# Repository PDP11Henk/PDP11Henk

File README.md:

- 👋 Hi, I’m @PDP11Henk, also a HAM radio amateur with the call-sign PA8PDP.
- 👀 I’m interested in building an F-16 simulator, building and playing with the Motorola 68000 / 68010 / 68020 microprocessors, and collecting PDP-11 hardware from D|I|G|I|T|A|L
- 🌱 I’m currently learning how to use Git  :) 
- 💞️ I’m looking to collaborate on integrating F-16 real instruments with home-made interface hardware to the Benchmark Systems BMS Simulator.
- 📫 How to reach me ...

<!---
PDP11Henk/PDP11Henk is a ✨ special ✨ repository because its `README.md` (this file) appears on your GitHub profile.
You can click the Preview link to take a look at your changes.
--->

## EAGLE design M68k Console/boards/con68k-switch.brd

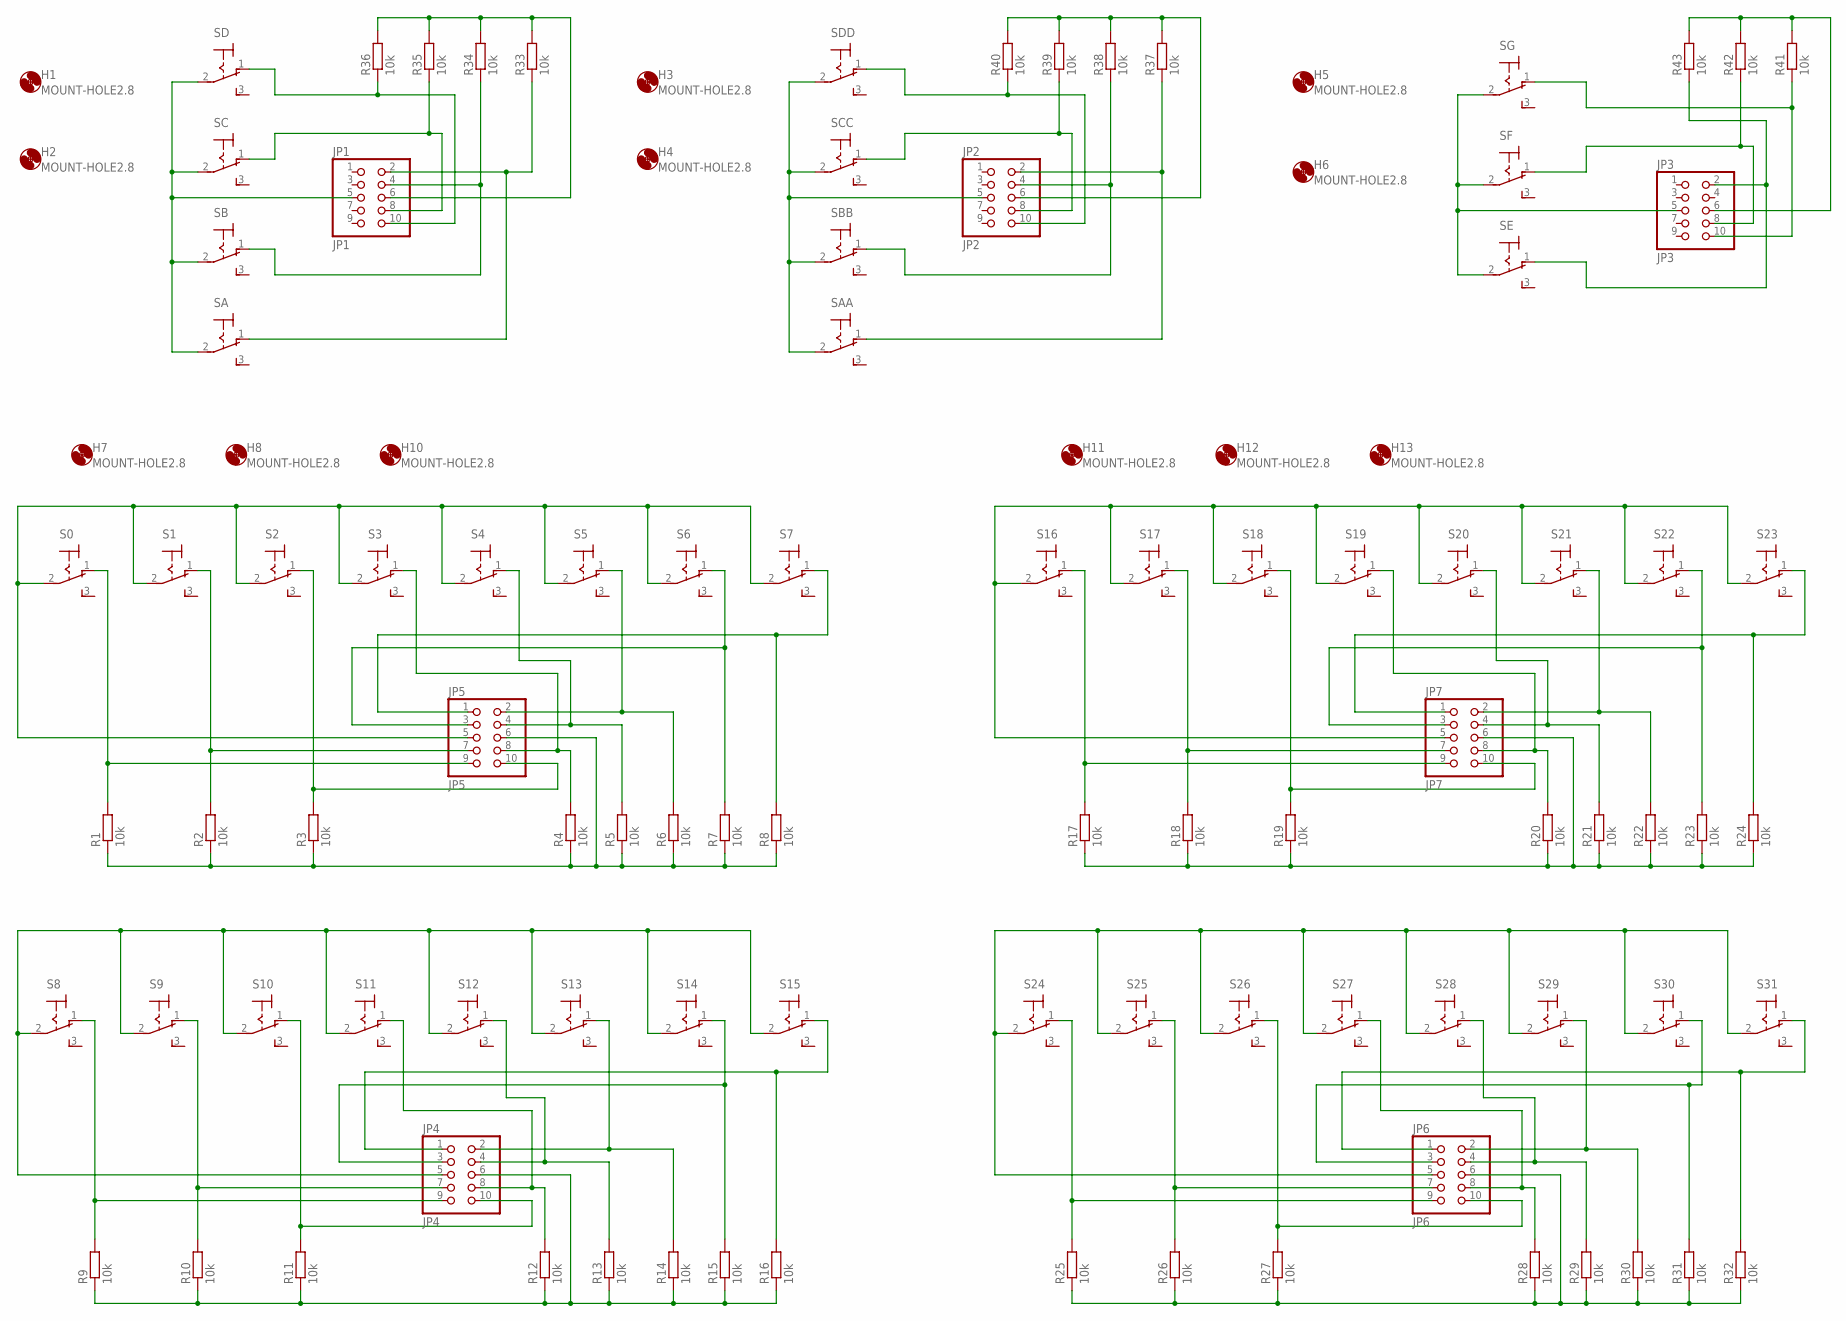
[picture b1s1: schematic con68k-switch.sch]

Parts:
H1, H2, H3, H4, H5, H6, H7, H8, H10, H11, H12, H13: MOUNT-HOLE2.8; 2,8
JP1: JP1; 2X05
JP2: JP2; 2X05
JP3: JP3; 2X05
JP4: JP4; 2X05
JP5: JP5; 2X05
JP6: JP6; 2X05
JP7: JP7; 2X05
R1, R2, R3, R4, R5, R6, R7, R8, R9, R10, R11, R12, R13, R14, R15, R16, R17, R18, R19, R20, R21, R22, R23, R24, R25, R26, R27, R28, R29, R30, R31, R32, R33, R34, R35, R36, R37, R38, R39, R40, R41, R42, R43: 10k; 0204/7
S0, S1, S2, S3, S4, S5, S6, S7, S8, S9, S10, S11, S12, S13, S14, S15, S16, S17, S18, S19, S20, S21, S22, S23, S24, S25, S26, S27, S28, S29, S30, S31: M9040P
SA: M9040P
SAA: M9040P
SB: M9040P
SBB: M9040P
SC: M9040P
SCC: M9040P
SD: M9040P
SDD: M9040P
SE: M9040P
SF: M9040P
SG: M9040P

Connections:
unnamed: JP1.2, R33.1, SA.1 (O)
unnamed: JP1.8, R35.1, SC.1 (O)
unnamed: JP1.10, R36.1, SD.1 (O)
unnamed: JP1.4, R34.1, SB.1 (O)
unnamed: JP1.6, R33.2, R34.2, R35.2, R36.2
unnamed: JP1.5, SA.2, SB.2, SC.2, SD.2
unnamed: JP2.8, R39.1, SCC.1 (O)
unnamed: JP2.10, R40.1, SDD.1 (O)
unnamed: JP2.5, SAA.2, SBB.2, SCC.2, SDD.2
unnamed: JP2.4, R38.1, SBB.1 (O)
unnamed: JP2.2, R37.1, SAA.1 (O)
unnamed: JP2.6, R37.2, R38.2, R39.2, R40.2
unnamed: JP3.5, SE.2, SF.2, SG.2
unnamed: JP3.2, R43.1, SE.1 (O)
unnamed: JP3.10, R41.1, SG.1 (O)
unnamed: JP3.6, R41.2, R42.2, R43.2
unnamed: JP3.8, R42.1, SF.1 (O)
unnamed: JP4.5, S8.2, S9.2, S10.2, S11.2, S12.2, S13.2, S14.2, S15.2
unnamed: JP4.3, R15.2, S14.1 (O)
unnamed: JP4.2, R14.2, S13.1 (O)
unnamed: JP4.4, R13.2, S12.1 (O)
unnamed: JP4.8, R12.2, S11.1 (O)
unnamed: JP4.10, R11.2, S10.1 (O)
unnamed: JP4.7, R10.2, S9.1 (O)
unnamed: JP4.9, R9.2, S8.1 (O)
unnamed: JP4.6, R9.1, R10.1, R11.1, R12.1, R13.1, R14.1, R15.1, R16.1
unnamed: JP4.1, R16.2, S15.1 (O)
unnamed: JP6.6, R25.1, R26.1, R27.1, R28.1, R29.1, R30.1, R31.1, R32.1
unnamed: JP6.3, R31.2, S30.1 (O)
unnamed: JP7.1, R24.2, S23.1 (O)
unnamed: JP7.3, R23.2, S22.1 (O)
unnamed: JP7.2, R22.2, S21.1 (O)
unnamed: JP5.5, S0.2, S1.2, S2.2, S3.2, S4.2, S5.2, S6.2, S7.2
unnamed: JP7.10, R19.2, S18.1 (O)
unnamed: JP5.6, R1.1, R2.1, R3.1, R4.1, R5.1, R6.1, R7.1, R8.1
unnamed: JP6.5, S24.2, S25.2, S26.2, S27.2, S28.2, S29.2, S30.2, S31.2
unnamed: JP6.2, R30.2, S29.1 (O)
unnamed: JP6.4, R29.2, S28.1 (O)
unnamed: JP6.8, R28.2, S27.1 (O)
unnamed: JP6.10, R27.2, S26.1 (O)
unnamed: JP6.7, R26.2, S25.1 (O)
unnamed: JP6.9, R25.2, S24.1 (O)
unnamed: JP5.1, R8.2, S7.1 (O)
unnamed: JP6.1, R32.2, S31.1 (O)
unnamed: JP5.3, R7.2, S6.1 (O)
unnamed: JP7.5, S16.2, S17.2, S18.2, S19.2, S20.2, S21.2, S22.2, S23.2
unnamed: JP7.4, R21.2, S20.1 (O)
unnamed: JP7.8, R20.2, S19.1 (O)
unnamed: JP5.9, R1.2, S0.1 (O)
unnamed: JP5.2, R6.2, S5.1 (O)
unnamed: JP5.4, R5.2, S4.1 (O)
unnamed: JP5.8, R4.2, S3.1 (O)
unnamed: JP5.10, R3.2, S2.1 (O)
unnamed: JP5.7, R2.2, S1.1 (O)
unnamed: JP7.7, R18.2, S17.1 (O)
unnamed: JP7.9, R17.2, S16.1 (O)
unnamed: JP7.6, R17.1, R18.1, R19.1, R20.1, R21.1, R22.1, R23.1, R24.1

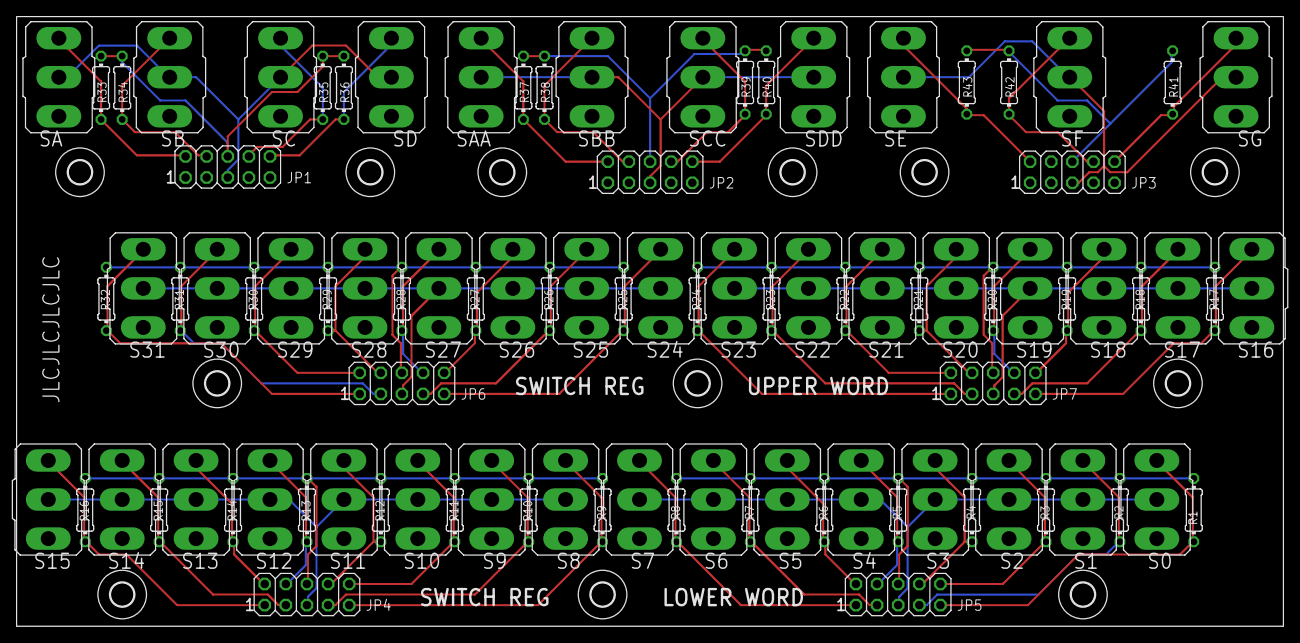
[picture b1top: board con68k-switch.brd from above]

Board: 2 copper layers, 152.4 x 73.3 mm, 105 parts (0 on the bottom side), 57 nets.

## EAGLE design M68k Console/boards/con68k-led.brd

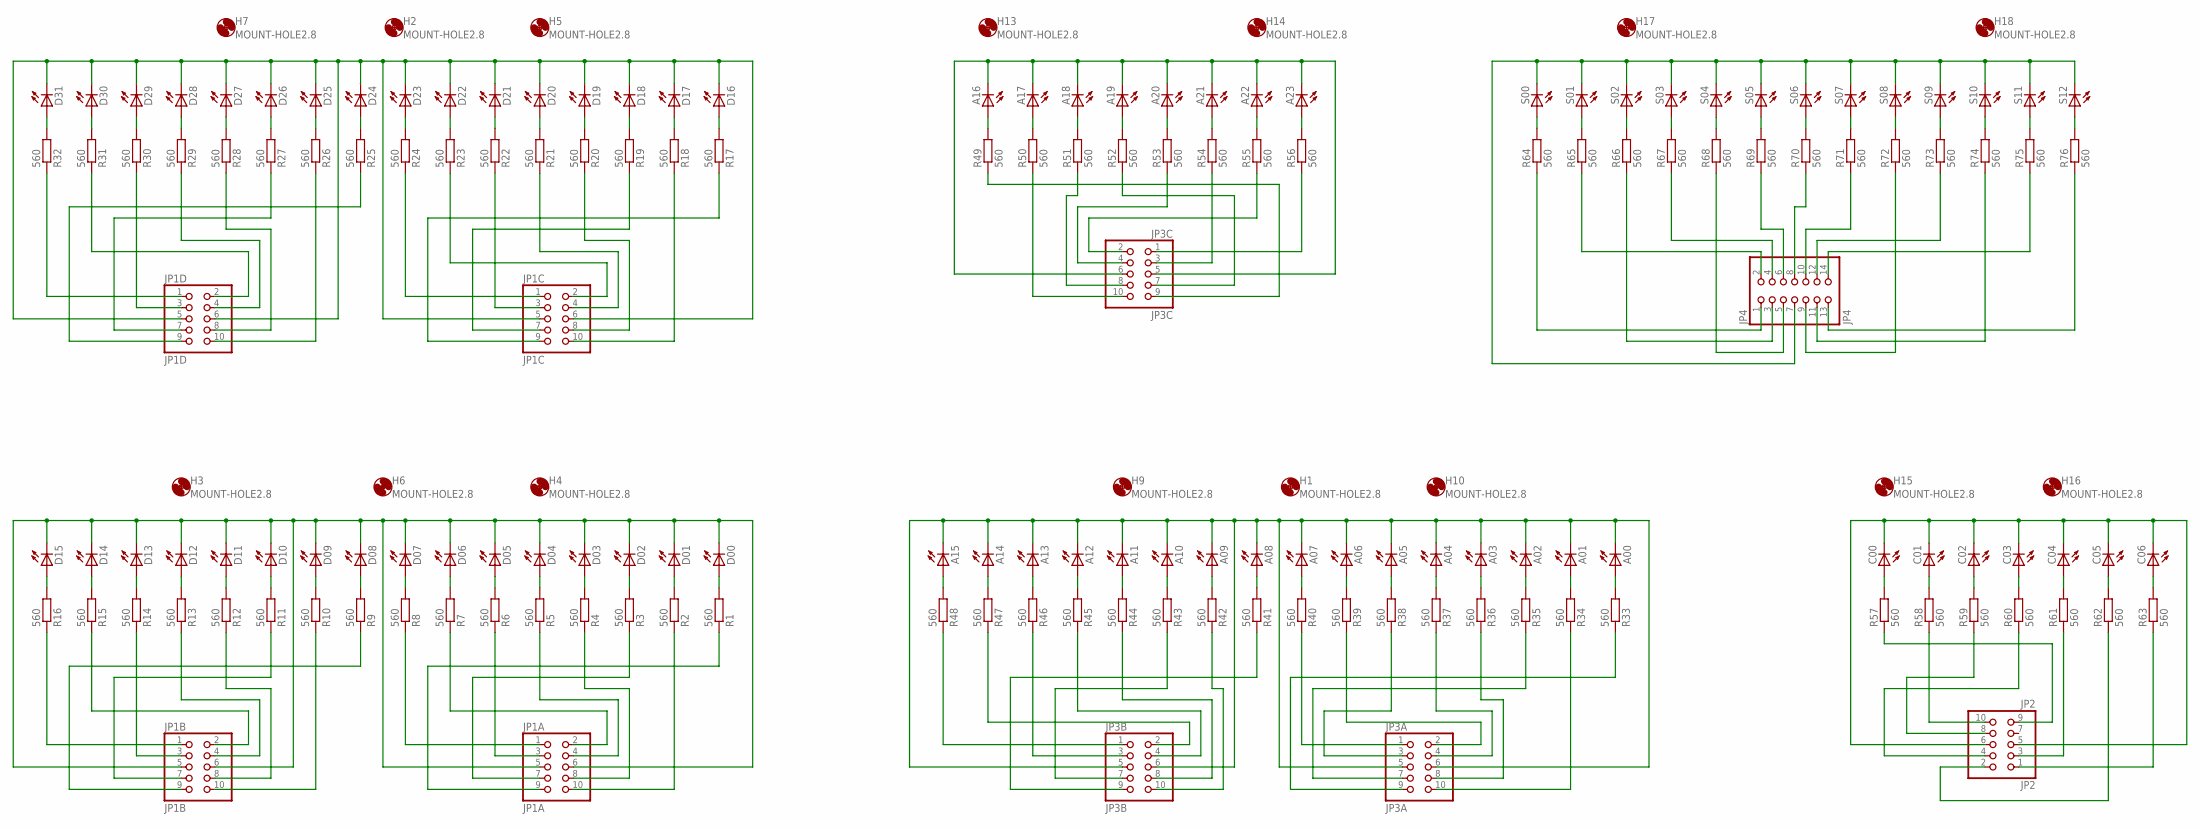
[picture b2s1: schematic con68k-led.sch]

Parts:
A00, A01, A02, A03, A04, A05, A06, A07, A08, A09, A10, A11, A12, A13, A14, A15, A16, A17, A18, A19, A20, A21, A22, A23: LED5MM
C00, C01, C02, C03, C04, C05, C06: LED5MM
D00, D01, D02, D03, D04, D05, D06, D07, D08, D09, D10, D11, D12, D13, D14, D15, D16, D17, D18, D19, D20, D21, D22, D23, D24, D25, D26, D27, D28, D29, D30, D31: LED5MM
H1, H2, H3, H4, H5, H6, H7, H9, H10, H13, H14, H15, H16, H17, H18: MOUNT-HOLE2.8; 2,8
JP1A: JP1A; 2X05
JP1B: JP1B; 2X05
JP1C: JP1C; 2X05
JP1D: JP1D; 2X05
JP2: JP2; 2X05
JP3A: JP3A; 2X05
JP3B: JP3B; 2X05
JP3C: JP3C; 2X05
JP4: JP4; 2X07
R1, R2, R3, R4, R5, R6, R7, R8, R9, R10, R11, R12, R13, R14, R15, R16, R17, R18, R19, R20, R21, R22, R23, R24, R25, R26, R27, R28, R29, R30, R31, R32, R33, R34, R35, R36, R37, R38, R39, R40, R41, R42, R43, R44, R45, R46, R47, R48, R49, R50, R51, R52, R53, R54, R55, R56, R57, R58, R59, R60, R61, R62, R63, R64, R65, R66, R67, R68, R69, R70, R71, R72, R73, R74, R75, R76: 560; 0204/7
S00, S01, S02, S03, S04, S05, S06, S07, S08, S09, S10, S11, S12: LED5MM

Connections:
unnamed: D00.K (C), D01.K (C), D02.K (C), D03.K (C), D04.K (C), D05.K (C), D06.K (C), D07.K (C), D08.K (C), D09.K (C), D10.K (C), D11.K (C), D12.K (C), D13.K (C), D14.K (C), D15.K (C), JP1A.5, JP1A.6, JP1B.5, JP1B.6
unnamed: D15.A, R16.2
unnamed: D14.A, R15.2
unnamed: D13.A, R14.2
unnamed: D12.A, R13.2
unnamed: D11.A, R12.2
unnamed: D10.A, R11.2
unnamed: D09.A, R10.2
unnamed: D08.A, R9.2
unnamed: D07.A, R8.2
unnamed: D06.A, R7.2
unnamed: D05.A, R6.2
unnamed: D04.A, R5.2
unnamed: D03.A, R4.2
unnamed: D02.A, R3.2
unnamed: D01.A, R2.2
unnamed: D00.A, R1.2
unnamed: JP1B.1, R16.1
unnamed: JP1B.2, R15.1
unnamed: JP1B.3, R14.1
unnamed: JP1B.4, R13.1
unnamed: JP1B.8, R12.1
unnamed: JP1B.7, R11.1
unnamed: JP1B.10, R10.1
unnamed: JP1B.9, R9.1
unnamed: JP1A.1, R8.1
unnamed: JP1A.2, R7.1
unnamed: JP1A.3, R6.1
unnamed: JP1A.4, R5.1
unnamed: JP1A.8, R4.1
unnamed: JP1A.7, R3.1
unnamed: JP1A.10, R2.1
unnamed: JP1A.9, R1.1
unnamed: D16.K (C), D17.K (C), D18.K (C), D19.K (C), D20.K (C), D21.K (C), D22.K (C), D23.K (C), D24.K (C), D25.K (C), D26.K (C), D27.K (C), D28.K (C), D29.K (C), D30.K (C), D31.K (C), JP1C.5, JP1C.6, JP1D.5, JP1D.6
unnamed: D31.A, R32.2
unnamed: D30.A, R31.2
unnamed: D29.A, R30.2
unnamed: D28.A, R29.2
unnamed: D27.A, R28.2
unnamed: D26.A, R27.2
unnamed: D25.A, R26.2
unnamed: D24.A, R25.2
unnamed: D23.A, R24.2
unnamed: D22.A, R23.2
unnamed: D21.A, R22.2
unnamed: D20.A, R21.2
unnamed: D19.A, R20.2
unnamed: D18.A, R19.2
unnamed: D17.A, R18.2
unnamed: D16.A, R17.2
unnamed: A15.A, R48.2
unnamed: JP1D.1, R32.1
unnamed: JP1D.2, R31.1
unnamed: JP1D.3, R30.1
unnamed: JP1D.4, R29.1
unnamed: JP1D.8, R28.1
unnamed: JP1D.7, R27.1
unnamed: JP1D.10, R26.1
unnamed: JP3B.1, R48.1
unnamed: JP1D.9, R25.1
unnamed: JP1C.1, R24.1
unnamed: JP1C.2, R23.1
unnamed: JP1C.3, R22.1
unnamed: JP1C.4, R21.1
unnamed: A14.A, R47.2
unnamed: JP1C.8, R20.1
unnamed: A00.K (C), A01.K (C), A02.K (C), A03.K (C), A04.K (C), A05.K (C), A06.K (C), A07.K (C), A08.K (C), A09.K (C), A10.K (C), A11.K (C), A12.K (C), A13.K (C), A14.K (C), A15.K (C), JP3A.5, JP3A.6, JP3B.5, JP3B.6
unnamed: A13.A, R46.2
unnamed: A12.A, R45.2
unnamed: A11.A, R44.2
unnamed: A10.A, R43.2
unnamed: A09.A, R42.2
unnamed: A08.A, R41.2
unnamed: A07.A, R40.2
unnamed: A06.A, R39.2
unnamed: A05.A, R38.2
unnamed: A04.A, R37.2
unnamed: A03.A, R36.2
unnamed: A02.A, R35.2
unnamed: A01.A, R34.2
unnamed: A00.A, R33.2
unnamed: A16.A, R49.2
unnamed: A17.A, R50.2
unnamed: JP3B.2, R47.1
unnamed: JP3B.3, R46.1
unnamed: JP3B.4, R45.1
unnamed: JP3A.1, R40.1
unnamed: JP3B.8, R44.1
unnamed: JP3B.7, R43.1
unnamed: JP4.1, R64.1
unnamed: JP3B.10, R42.1
unnamed: JP4.2, R65.1
unnamed: JP3B.9, R41.1
unnamed: JP3A.2, R39.1
unnamed: JP3A.3, R38.1
unnamed: JP3A.4, R37.1
unnamed: JP3A.8, R36.1
unnamed: JP3A.7, R35.1
unnamed: JP3A.10, R34.1
unnamed: A16.K (C), A17.K (C), A18.K (C), A19.K (C), A20.K (C), A21.K (C), A22.K (C), A23.K (C), JP3C.5, JP3C.6
unnamed: A18.A, R51.2
unnamed: A19.A, R52.2
unnamed: A20.A, R53.2
unnamed: A21.A, R54.2
unnamed: A22.A, R55.2
unnamed: A23.A, R56.2
unnamed: R64.2, S00.A
unnamed: R65.2, S01.A
unnamed: JP2.1, R63.1
unnamed: JP3C.1, R56.1
unnamed: JP3C.2, R55.1
unnamed: JP3C.3, R54.1
unnamed: JP3C.4, R53.1
unnamed: JP3C.7, R52.1
unnamed: JP3C.8, R51.1
unnamed: JP3C.10, R50.1
unnamed: JP3C.9, R49.1
unnamed: C00.K (C), C01.K (C), C02.K (C), C03.K (C), C04.K (C), C05.K (C), C06.K (C), JP2.5, JP2.6
unnamed: C00.A, R57.2
unnamed: C01.A, R58.2
unnamed: C02.A, R59.2
unnamed: C03.A, R60.2
unnamed: C04.A, R61.2
unnamed: C05.A, R62.2
unnamed: C06.A, R63.2
unnamed: JP2.2, R62.1
unnamed: JP2.3, R61.1
unnamed: JP2.4, R60.1
unnamed: JP2.9, R57.1
unnamed: JP2.10, R58.1
unnamed: JP2.8, R59.1
unnamed: JP4.7, S00.K (C), S01.K (C), S02.K (C), S03.K (C), S04.K (C), S05.K (C), S06.K (C), S07.K (C), S08.K (C), S09.K (C), S10.K (C), S11.K (C), S12.K (C)
unnamed: R66.2, S02.A
unnamed: R67.2, S03.A
unnamed: R68.2, S04.A
unnamed: R69.2, S05.A
unnamed: R70.2, S06.A
unnamed: R71.2, S07.A
unnamed: R72.2, S08.A
unnamed: R73.2, S09.A
unnamed: R74.2, S10.A
unnamed: R75.2, S11.A
unnamed: R76.2, S12.A
unnamed: JP4.3, R66.1
unnamed: JP4.4, R67.1
unnamed: JP4.5, R68.1
unnamed: JP4.6, R69.1
unnamed: JP4.13, R76.1
unnamed: JP4.14, R75.1
unnamed: JP4.11, R74.1
unnamed: JP4.12, R73.1
unnamed: JP4.9, R72.1
unnamed: JP4.10, R71.1
unnamed: JP4.8, R70.1
unnamed: JP3A.9, R33.1
unnamed: JP1C.7, R19.1
unnamed: JP1C.10, R18.1
unnamed: JP1C.9, R17.1

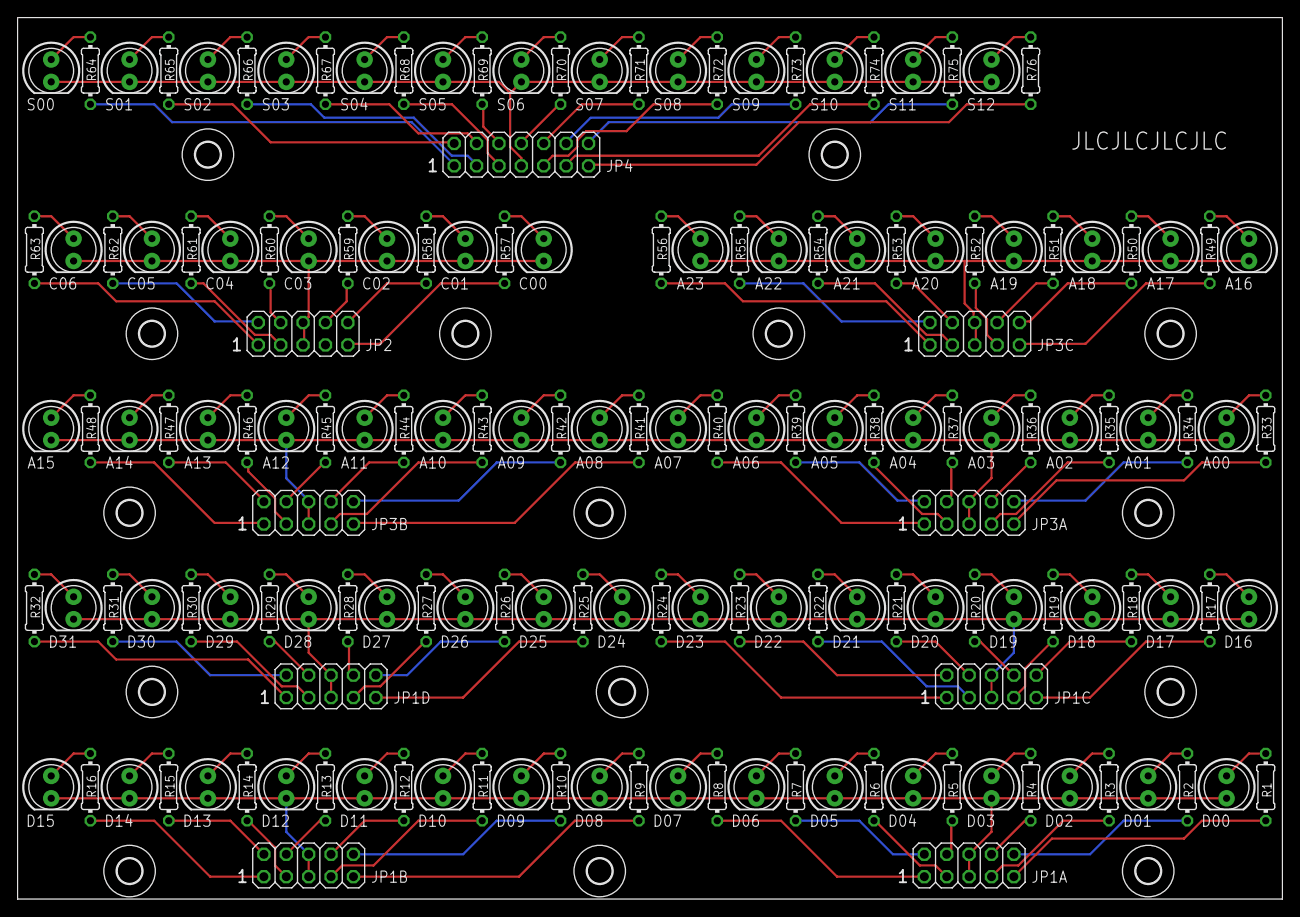
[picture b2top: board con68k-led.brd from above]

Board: 2 copper layers, 143.5 x 100.0 mm, 176 parts (0 on the bottom side), 158 nets.

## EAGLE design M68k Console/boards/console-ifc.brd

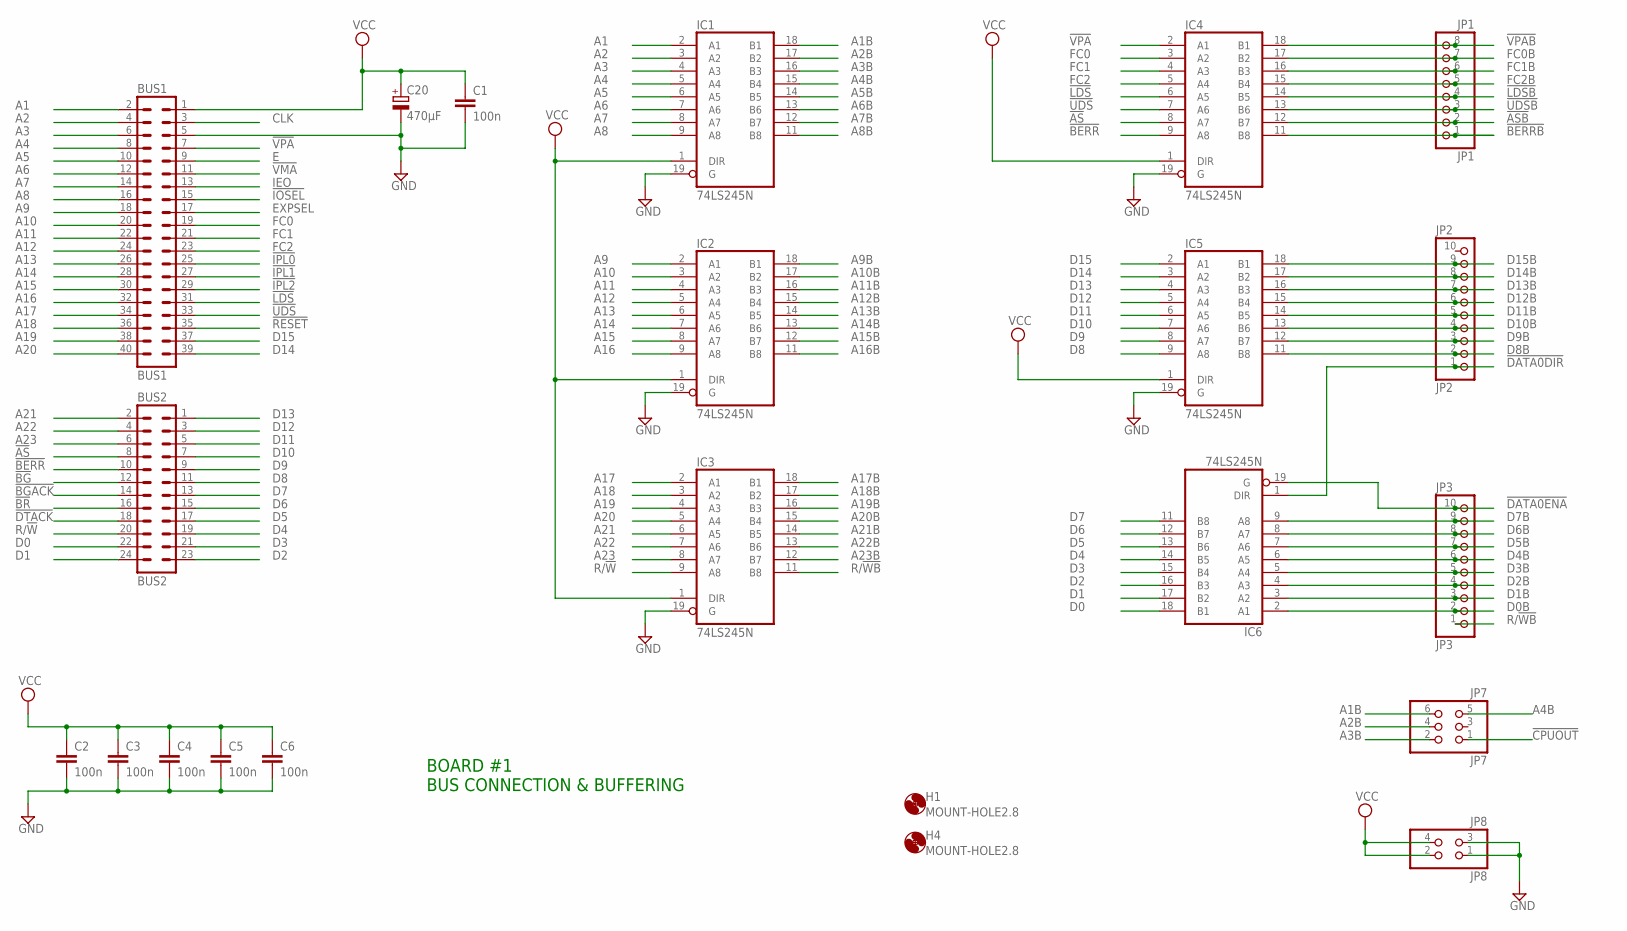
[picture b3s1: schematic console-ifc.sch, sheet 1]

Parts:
BUS1: BUS1; MA20-2
BUS2: BUS2; MA12-2
C1, C2, C3, C4, C5, C6: 100n; C025-024X044
C20: 470µF; E2,5-7
H1, H4: MOUNT-HOLE2.8; 2,8
IC1, IC2, IC3, IC4, IC5, IC6: 74LS245N; DIL20
JP1: JP1; 1X08
JP2: JP2; 1X10
JP3: JP3; 1X10
JP7: JP7; 2X03
JP8: JP8; 2X02

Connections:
!AS: BUS2.8, IC4.8 (A7)
!ASB: IC4.12 (B7), JP1.2; also elsewhere on the board
!BERR: BUS2.10, IC4.9 (A8)
!BERRB: IC4.11 (B8), JP1.1
!BG: BUS2.12
!BGACK: BUS2.14
!BR: BUS2.16
!CPUOUT: JP7.1; also elsewhere on the board
!DATA0DIR: IC6.1 (DIR), JP2.1
!DATA0ENA: IC6.19 (G), JP3.10
!DTACK: BUS2.18; also elsewhere on the board
!IOSEL: BUS1.15; also elsewhere on the board
!IPL0: BUS1.25; also elsewhere on the board
!IPL1: BUS1.27; also elsewhere on the board
!IPL2: BUS1.29; also elsewhere on the board
!LDS: BUS1.31, IC4.6 (A5)
!LDSB: IC4.14 (B5), JP1.4; also elsewhere on the board
!RESET: BUS1.35; also elsewhere on the board
!UDS: BUS1.33, IC4.7 (A6)
!UDSB: IC4.13 (B6), JP1.3
!VMA: BUS1.11
!VPA: BUS1.7, IC4.2 (A1); also elsewhere on the board
!VPAB: IC4.18 (B1), JP1.8
A1: BUS1.2, IC1.2 (A1)
A1B: IC1.18 (B1), JP7.6; also elsewhere on the board
A2: BUS1.4, IC1.3 (A2)
A2B: IC1.17 (B2), JP7.4; also elsewhere on the board
A3: BUS1.6, IC1.4 (A3)
A3B: IC1.16 (B3), JP7.2; also elsewhere on the board
A4: BUS1.8, IC1.5 (A4)
A4B: IC1.15 (B4), JP7.5; also elsewhere on the board
A5: BUS1.10, IC1.6 (A5)
A5B: IC1.14 (B5); also elsewhere on the board
A6: BUS1.12, IC1.7 (A6)
A6B: IC1.13 (B6); also elsewhere on the board
A7: BUS1.14, IC1.8 (A7)
A7B: IC1.12 (B7); also elsewhere on the board
A8: BUS1.16, IC1.9 (A8)
A8B: IC1.11 (B8); also elsewhere on the board
A9: BUS1.18, IC2.2 (A1)
A9B: IC2.18 (B1); also elsewhere on the board
A10: BUS1.20, IC2.3 (A2)
A10B: IC2.17 (B2); also elsewhere on the board
A11: BUS1.22, IC2.4 (A3)
A11B: IC2.16 (B3); also elsewhere on the board
A12: BUS1.24, IC2.5 (A4)
A12B: IC2.15 (B4); also elsewhere on the board
A13: BUS1.26, IC2.6 (A5)
A13B: IC2.14 (B5); also elsewhere on the board
A14: BUS1.28, IC2.7 (A6)
A14B: IC2.13 (B6); also elsewhere on the board
A15: BUS1.30, IC2.8 (A7)
A15B: IC2.12 (B7); also elsewhere on the board
A16: BUS1.32, IC2.9 (A8)
A16B: IC2.11 (B8); also elsewhere on the board
A17: BUS1.34, IC3.2 (A1)
A17B: IC3.18 (B1); also elsewhere on the board
A18: BUS1.36, IC3.3 (A2)
A18B: IC3.17 (B2); also elsewhere on the board
A19: BUS1.38, IC3.4 (A3)
A19B: IC3.16 (B3); also elsewhere on the board
A20: BUS1.40, IC3.5 (A4)
A20B: IC3.15 (B4); also elsewhere on the board
A21: BUS2.2, IC3.6 (A5)
A21B: IC3.14 (B5); also elsewhere on the board
A22: BUS2.4, IC3.7 (A6)
A22B: IC3.13 (B6); also elsewhere on the board
A23: BUS2.6, IC3.8 (A7)
A23B: IC3.12 (B7); also elsewhere on the board
CLK: BUS1.3
D0: BUS2.22, IC6.18 (B1)
D0B: IC6.2 (A1), JP3.2; also elsewhere on the board
D1: BUS2.24, IC6.17 (B2)
D1B: IC6.3 (A2), JP3.3; also elsewhere on the board
D2: BUS2.23, IC6.16 (B3)
D2B: IC6.4 (A3), JP3.4; also elsewhere on the board
D3: BUS2.21, IC6.15 (B4)
D3B: IC6.5 (A4), JP3.5; also elsewhere on the board
D4: BUS2.19, IC6.14 (B5)
D4B: IC6.6 (A5), JP3.6; also elsewhere on the board
D5: BUS2.17, IC6.13 (B6)
D5B: IC6.7 (A6), JP3.7; also elsewhere on the board
D6: BUS2.15, IC6.12 (B7)
D6B: IC6.8 (A7), JP3.8; also elsewhere on the board
D7: BUS2.13, IC6.11 (B8)
D7B: IC6.9 (A8), JP3.9; also elsewhere on the board
D8: BUS2.11, IC5.9 (A8)
D8B: IC5.11 (B8), JP2.2
D9: BUS2.9, IC5.8 (A7)
D9B: IC5.12 (B7), JP2.3
D10: BUS2.7, IC5.7 (A6)
D10B: IC5.13 (B6), JP2.4
D11: BUS2.5, IC5.6 (A5)
D11B: IC5.14 (B5), JP2.5
D12: BUS2.3, IC5.5 (A4)
D12B: IC5.15 (B4), JP2.6
D13: BUS2.1, IC5.4 (A3)
D13B: IC5.16 (B3), JP2.7
D14: BUS1.39, IC5.3 (A2)
D14B: IC5.17 (B2), JP2.8
D15: BUS1.37, IC5.2 (A1)
D15B: IC5.18 (B1), JP2.9
E: BUS1.9
EXPSEL: BUS1.17
FC0: BUS1.19, IC4.3 (A2)
FC0B: IC4.17 (B2), JP1.7; also elsewhere on the board
FC1: BUS1.21, IC4.4 (A3)
FC1B: IC4.16 (B3), JP1.6; also elsewhere on the board
FC2: BUS1.23, IC4.5 (A4)
FC2B: IC4.15 (B4), JP1.5; also elsewhere on the board
GND: BUS1.5, C1.2, C2.2, C3.2, C4.2, C5.2, C6.2, C20.-, IC1.10 (GND), IC1.19 (G), IC2.10 (GND), IC2.19 (G), IC3.10 (GND), IC3.19 (G), IC4.10 (GND), IC4.19 (G), IC5.10 (GND), IC5.19 (G), IC6.10 (GND), JP8.1, JP8.3; also elsewhere on the board
IEO: BUS1.13
R/!W: BUS2.20, IC3.9 (A8)
R/!WB: IC3.11 (B8), JP3.1
VCC: BUS1.1, C1.1, C2.1, C3.1, C4.1, C5.1, C6.1, C20.+, IC1.1 (DIR), IC1.20 (VCC), IC2.1 (DIR), IC2.20 (VCC), IC3.1 (DIR), IC3.20 (VCC), IC4.1 (DIR), IC4.20 (VCC), IC5.1 (DIR), IC5.20 (VCC), IC6.20 (VCC), JP8.2, JP8.4; also elsewhere on the board

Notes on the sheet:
BOARD #1 BUS CONNECTION & BUFFERING

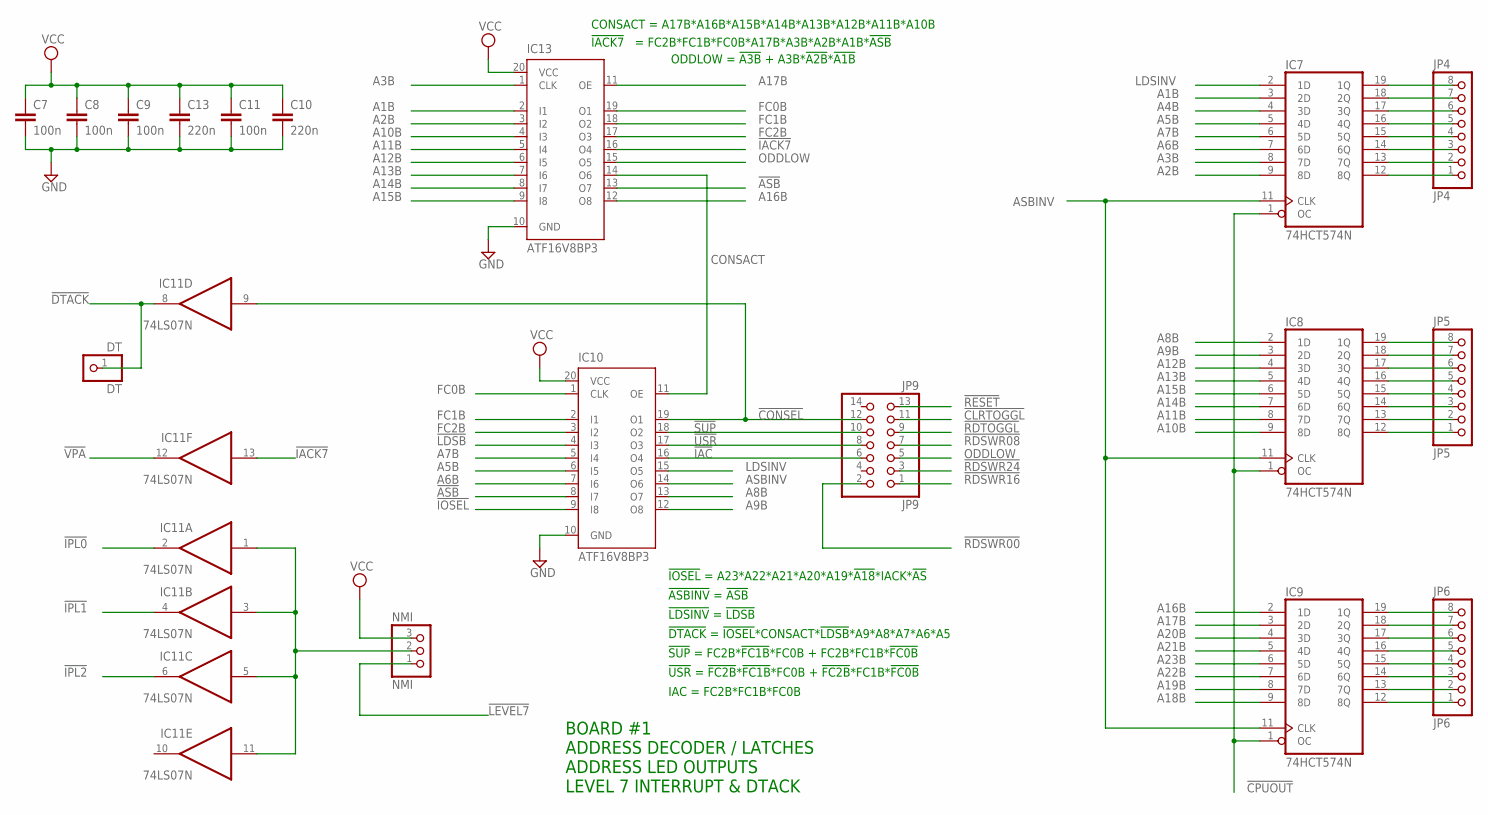
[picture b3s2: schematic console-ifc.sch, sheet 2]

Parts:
C7, C8, C9, C11: 100n; C025-024X044
C10, C13: 220n; C025-024X044
DT: DT; 1X01
IC7, IC8, IC9: 74HCT574N; DIL20
IC10, IC13: ATF16V8BP3; DIL20
IC11: 74LS07N; DIL14
JP4: JP4; 1X08
JP5: JP5; 1X08
JP6: JP6; 1X08
JP9: JP9; 2X07
NMI: NMI; 1X03

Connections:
!ASB: IC10.8 (I7), IC13.13 (O7); also elsewhere on the board
!CLRTOGGL: JP9.11; also elsewhere on the board
!CONSEL: IC10.19 (O1), IC11.9 (I), JP9.12
!CPUOUT: IC7.1 (OC), IC8.1 (OC), IC9.1 (OC); also elsewhere on the board
!DTACK: DT.1, IC11.8 (O); also elsewhere on the board
!IAC: IC10.16 (O4), JP9.6
!IACK7: IC11.13 (I), IC13.16 (O4); also elsewhere on the board
!IOSEL: IC10.9 (I8); also elsewhere on the board
!IPL0: IC11.2 (O); also elsewhere on the board
!IPL1: IC11.4 (O); also elsewhere on the board
!IPL2: IC11.6 (O); also elsewhere on the board
!LDSB: IC10.4 (I3); also elsewhere on the board
!LEVEL7: NMI.1; also elsewhere on the board
!RDSWR00: JP9.2; also elsewhere on the board
!RDSWR08: JP9.7; also elsewhere on the board
!RDSWR16: JP9.1; also elsewhere on the board
!RDSWR24: JP9.3; also elsewhere on the board
!RDTOGGL: JP9.9; also elsewhere on the board
!RESET: JP9.13; also elsewhere on the board
!SUP: IC10.18 (O2), JP9.10
!USR: IC10.17 (O3), JP9.8
!VPA: IC11.12 (O); also elsewhere on the board
A1B: IC7.3 (2D), IC13.2 (I1); also elsewhere on the board
A2B: IC7.9 (8D), IC13.3 (I2); also elsewhere on the board
A3B: IC7.8 (7D), IC13.1 (CLK); also elsewhere on the board
A4B: IC7.4 (3D); also elsewhere on the board
A5B: IC7.5 (4D), IC10.6 (I5); also elsewhere on the board
A6B: IC7.7 (6D), IC10.7 (I6); also elsewhere on the board
A7B: IC7.6 (5D), IC10.5 (I4); also elsewhere on the board
A8B: IC8.2 (1D), IC10.13 (O7); also elsewhere on the board
A9B: IC8.3 (2D), IC10.12 (O8); also elsewhere on the board
A10B: IC8.9 (8D), IC13.4 (I3); also elsewhere on the board
A11B: IC8.8 (7D), IC13.5 (I4); also elsewhere on the board
A12B: IC8.4 (3D), IC13.6 (I5); also elsewhere on the board
A13B: IC8.5 (4D), IC13.7 (I6); also elsewhere on the board
A14B: IC8.7 (6D), IC13.8 (I7); also elsewhere on the board
A15B: IC8.6 (5D), IC13.9 (I8); also elsewhere on the board
A16B: IC9.2 (1D), IC13.12 (O8); also elsewhere on the board
A17B: IC9.3 (2D), IC13.11 (OE); also elsewhere on the board
A18B: IC9.9 (8D); also elsewhere on the board
A19B: IC9.8 (7D); also elsewhere on the board
A20B: IC9.4 (3D); also elsewhere on the board
A21B: IC9.5 (4D); also elsewhere on the board
A22B: IC9.7 (6D); also elsewhere on the board
A23B: IC9.6 (5D); also elsewhere on the board
ASBINV: IC7.11 (CLK), IC8.11 (CLK), IC9.11 (CLK), IC10.14 (O6)
CONSACT: IC10.11 (OE), IC13.14 (O6)
FC0B: IC10.1 (CLK), IC13.19 (O1); also elsewhere on the board
FC1B: IC10.2 (I1), IC13.18 (O2); also elsewhere on the board
FC2B: IC10.3 (I2), IC13.17 (O3); also elsewhere on the board
GND: C7.2, C8.2, C9.2, C10.2, C11.2, C13.2, IC7.10 (GND), IC8.10 (GND), IC9.10 (GND), IC10.10 (GND), IC11.7 (GND), IC13.10 (GND); also elsewhere on the board
LDSINV: IC7.2 (1D), IC10.15 (O5)
unnamed: IC7.19 (1Q), JP4.8
unnamed: IC11.1 (I), IC11.3 (I), IC11.5 (I), IC11.11 (I), NMI.2
unnamed: IC8.19 (1Q), JP5.8
unnamed: IC7.18 (2Q), JP4.7
unnamed: IC7.17 (3Q), JP4.6
unnamed: IC7.16 (4Q), JP4.5
unnamed: IC7.15 (5Q), JP4.4
unnamed: IC7.14 (6Q), JP4.3
unnamed: IC7.13 (7Q), JP4.2
unnamed: IC7.12 (8Q), JP4.1
unnamed: IC8.18 (2Q), JP5.7
unnamed: IC8.17 (3Q), JP5.6
unnamed: IC8.16 (4Q), JP5.5
unnamed: IC8.15 (5Q), JP5.4
unnamed: IC8.14 (6Q), JP5.3
unnamed: IC8.13 (7Q), JP5.2
unnamed: IC8.12 (8Q), JP5.1
unnamed: IC9.19 (1Q), JP6.8
unnamed: IC9.18 (2Q), JP6.7
unnamed: IC9.17 (3Q), JP6.6
unnamed: IC9.16 (4Q), JP6.5
unnamed: IC9.15 (5Q), JP6.4
unnamed: IC9.14 (6Q), JP6.3
unnamed: IC9.13 (7Q), JP6.2
unnamed: IC9.12 (8Q), JP6.1
ODDLOW: IC13.15 (O5), JP9.5
VCC: C7.1, C8.1, C9.1, C10.1, C11.1, C13.1, IC7.20 (VCC), IC8.20 (VCC), IC9.20 (VCC), IC10.20 (VCC), IC11.14 (VCC), IC13.20 (VCC), NMI.3; also elsewhere on the board

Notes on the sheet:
BOARD #1 ADDRESS DECODER / LATCHES ADDRESS LED OUTPUTS LEVEL 7 INTERRUPT & DTACK
CONSACT = A17B*A16B*A15B*A14B*A13B*A12B*A11B*A10B
!IACK7! = FC2B*FC1B*FC0B*A17B*A3B*A2B*A1B*!ASB
!DTACK! = !IOSEL!*CONSACT*!LDSB!*A9*A8*A7*A6*A5
!ASBINV! = !ASB
!IOSEL! = A23*A22*A21*A20*A19*!A18!*IACK*!AS
!SUP! = FC2B*!FC1B!*FC0B + FC2B*FC1B*!FC0B
!USR! = !FC2B!*!FC1B!*FC0B + !FC2B!*FC1B*!FC0B
IAC = FC2B*FC1B*FC0B
!LDSINV! = !LDSB
ODDLOW = !A3B! + A3B*!A2B!*!A1B!

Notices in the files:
parts and their libraries:
henk: Licensing: CC v3.0 Share-Alike You are welcome to use this library for commercial purposes.
